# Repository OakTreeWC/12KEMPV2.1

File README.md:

# 12KEMP V2.1  (Complete)
12KEMP V2.1 is a 12 key 4 by 3 macropad, that features a Xiao SEEED Studio RP2040 with vial-qmk support, a clickable rotary encoder, a completely custom pcb with hot-swap support for 3/5-pin regular MX switches, as well as a complete case. All related files are in this repo, and you may create any form of case to mount the pcb onto, though it may take some time. Additionally, a bill of materials (BOM) is included. 

I made this project, 1. for school, and 2. for the [hackclub blueprint](https://blueprint.hackclub.com) event.

## Installing the Firmware
In order to install the firmware on the SEEED Studio RP2040 (RP2350 is not supported in QMK yet), hold the boot button on the microcontroller while plugging it into your computer. Once plugged in, a USB Mass Storage Device should appear. Download and move the .uf2 [firmware file](https://github.com/OakTreeWC/12KEMPV2.1/raw/refs/heads/main/Production/firmware.uf2) to the device. After the firmware has been put on the flash, the microcontroller should restart automatically. The firmware has now been installed.

## Usage
In order to use this project, one can either download Vial from [get.vial.today](https://get.vial.today), or use their [web interface](https://vial.rocks/). When plugged in, the device should show up on the top in a little dropdown. (Web users may have to manually select the device when setting up) If necessary, select the device from the dropdown. Now you can manually change what each key on the macropad does, simply by clicking the key you want to change and selecting what you want it to do from the bottom. You can change what keys on the other layers do as well, by just clicking the numbers right under the dropdown on the left.

## Bill of Materials
|Item                  |Description                                                                        |Qty.|Unit Price (USD)|Total Price  (USD)|URL                                                                                                                                                                                                                                                                                                                                                                                                                                                                                                         |Running Total (USD + Tax)|
|----------------------|-----------------------------------------------------------------------------------|----|----------------|------------------|------------------------------------------------------------------------------------------------------------------------------------------------------------------------------------------------------------------------------------------------------------------------------------------------------------------------------------------------------------------------------------------------------------------------------------------------------------------------------------------------------------|-------------------------|
|XIAO RP2040    |ARM® Cortex®-M0+ MCU 32-Bit Embedded Evaluation Board                              |1   |$4.68           |$4.68             |https://www.digikey.com/en/products/detail/seeed-technology-co-ltd/102010428/14672129                                                                                                                                                                                                                                                                                                                                                                                                                       |$5.16                    |
|Rotary Encoder        |Rotary Encoder Incremental 24 Quadrature (Incremental) Horizontal                  |1   |$1.72           |$1.72             |https://www.digikey.com/en/products/detail/bourns-inc/PEC12R-4020F-S0024/4699271                                                                                                                                                                                                                                                                                                                                                                                                                            |$7.06                    |
|Reverse Neopixels     |Addressable Lighting - 10 LED Discrete Red, Green, Blue (RGB)                      |2   |$2.95           |$5.90             |https://www.digikey.com/en/products/detail/adafruit-industries-llc/4960/14302512                                                                                                                                                                                                                                                                                                                                                                                                                            |$13.56                   |
|Akko Keyboard Switches|Akko V3 Creamy Yellow Pro Keyboard Switch, 5-Pin 50gf Linear Switches (45pcs)      |1   |$12.99          |$12.99            |https://www.amazon.com/Akko-Keyboard-Dustproof-Mechanical-Switches/dp/B0C3H8NVJV                                                                                                                                                                                                                                                                                                                                                                                                                            |$27.88                   |
|Schottky Diodes       |Diode 30 V 200mA Surface Mount 0603                                                |12  |$0.10           |$1.18             |https://www.digikey.com/en/products/detail/taiwan-semiconductor-corporation/TSS54U-RGG/7360711                                                                                                                                                                                                                                                                                                                                                                                                              |$29.18                   |
|Resistor              |For Neopixel Data Line. 379 Ohms ±0.1% 0.1W, 1/10W Chip Resistor 0603 (1608 Metric)|1   |$0.12           |$0.12             |https://www.digikey.com/en/products/detail/koa-speer-electronics-inc/RN73R1JTTD3790B25/10016392                                                                                                                                                                                                                                                                                                                                                                                                             |$29.31                   |
|PCB                   |PCB Manufactured by JLCPCB. White, 1.6mm, HASL w/ lead                             |5   |$1.32           |$6.60             |https://jlcpcb.com                                                                                                                                                                                                                                                                                                                                                                                                                                                                                          |$36.59                   |
|Lower Case            |Case Manufactured by JLC3DP. Black Resin                                           |1   |$12.47          |$12.47            |https://jlc3dp.com                                                                                                                                                                                                                                                                                                                                                                                                                                                                                          |$50.34                   |
|Upper Case            |Case Manufactured by JLCPCB. Grey Resin                                            |1   |$2.51           |$2.51             |https://jlc3dp.com                                                                                                                                                                                                                                                                                                                                                                                                                                                                                          |$53.11                   |
|Keycaps               |DSA Keycaps White 24pcs                                                            |1   |$8.99           |$8.99             |www.amazon.com/Mechkeeb-Profile-Switches-Keyboard-Replacement/dp/B0BWDTBF1L                                                                                                                                                                                                                                                                                                                                                                                                                                 |$63.02                   |
|Rotary Encoder Knob   |Aluminum Rotary Encoder Knob 2pcs                                                  |1   |$8.99           |$8.99             |www.amazon.com/Szliyands-Aluminum-Electronic-Potentiometer-Knob，Switch/dp/B099PX52LW                                                                                                                                                                                                                                                                                                                                                                                                                        |$72.93                   |
|Threaded Inserts      |M3 Threaded Inserts 152pcs                                                         |1   |$6.99           |$6.99             |https://www.amazon.com/Vibit-Threaded-Soldering-Printing-Components/dp/B0FWWW8VP1/ref=sr_1_3                                                                                                                                                                                                                                                                                                                                                                                                                |$80.64                   |
|Machine Screws        |M3 Screw Kit                                                                       |1   |$9.99           |$9.99             |https://www.amazon.com/Fgruh-750PCS-Assortment-Washers-Assorted/dp/B0FGV5FCBN/ref=sr_1_3?crid=2UNAGQJ7TRSPF&dib=eyJ2IjoiMSJ9.T3HWVrCMzkskj4FDtvfCYjAhiKf2eIXJNrTn39_bFjBR1J806O1NskeC_TrNL2d-0_rv4c3tJ2WiIqImzYRsNdlKskiq_KPhw2MnuLHrr7ROWvp0aYAezCjHHAfx-j9R1FgRYMZR6z3j6DWbe_FTcKSI5cNCdqJEDhLnH9UyM0u5ed6Of07kpRqKBp5WkTLn8qUsW4GWJz8Y-hXZX6mGeCbl1zGSf24ox8LtrZCSgZs.QTs0QwFb8cDs_wXvUWLPa0GUjuv97zXGykg1SJQzuNE&dib_tag=se&keywords=m3+screw+set&qid=1771132139&sprefix=m3+screw+set%2Caps%2C211&sr=8-3|$91.65                   |
|Digikey Shipping      |                                                                                   |1   |$4.99           |$4.99             |                                                                                                                                                                                                                                                                                                                                                                                                                                                                                                            |$97.15                  |
|JLC Shipping          |                                                                                   |1   |$10.73          |$10.73             |                                                                                                                                                                                                                                                                                                                                                                                                                                                                                                            |$108.98                  |

## Licensing

Copyright 2026 William C.

Licensed under the Apache License, Version 2.0 (the "License");
you may not use this file except in compliance with the License.
You may obtain a copy of the License at

http://www.apache.org/licenses/LICENSE-2.0

Unless required by applicable law or agreed to in writing, software
distributed under the License is distributed on an "AS IS" BASIS,
WITHOUT WARRANTIES OR CONDITIONS OF ANY KIND, either express or implied.
See the License for the specific language governing permissions and
limitations under the License.

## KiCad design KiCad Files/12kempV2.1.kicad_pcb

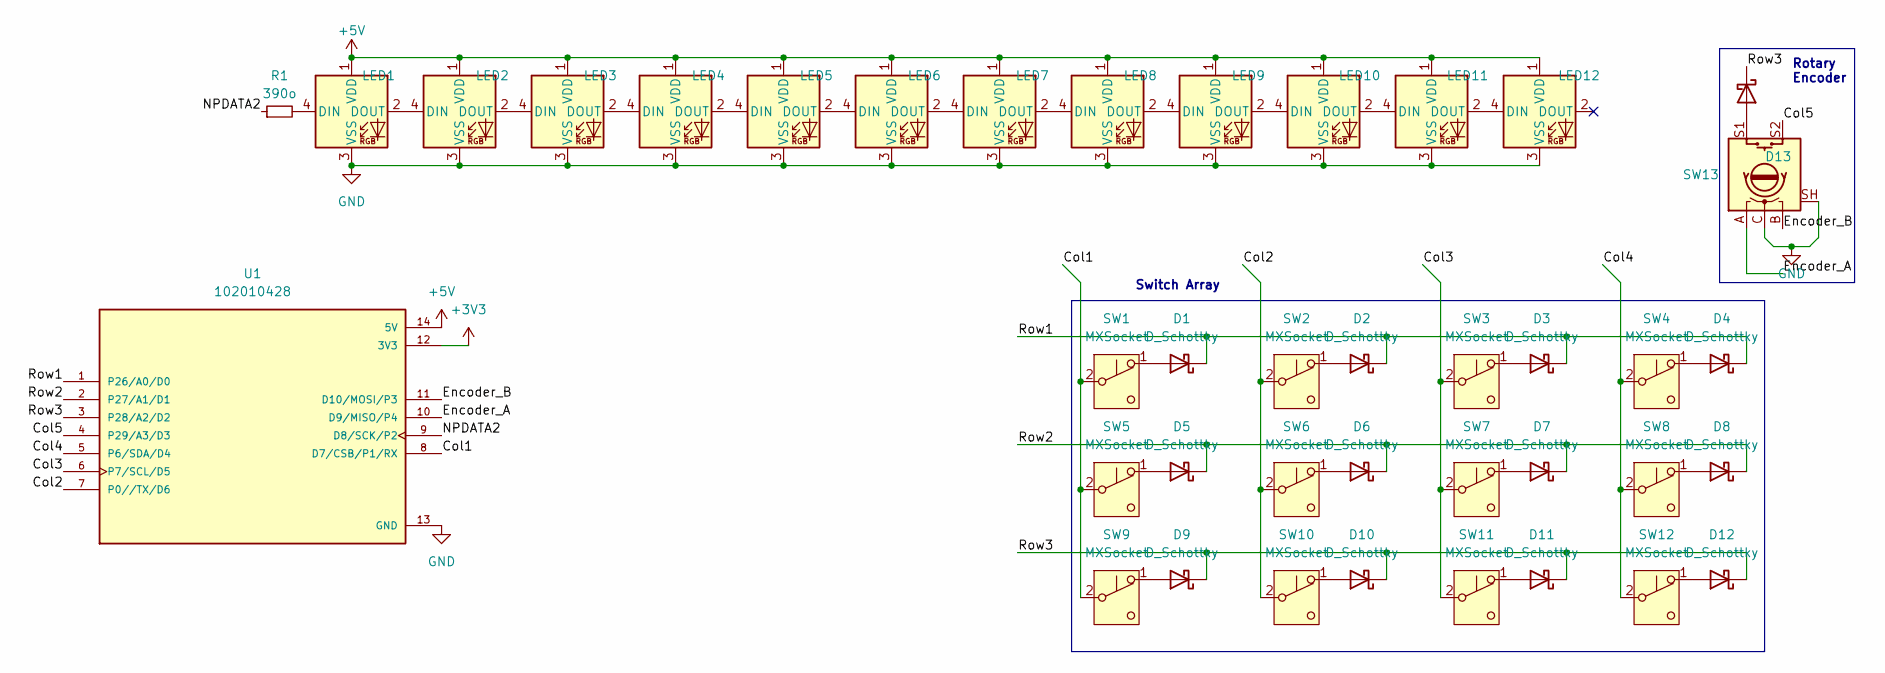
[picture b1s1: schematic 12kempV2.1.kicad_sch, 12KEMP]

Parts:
D1, D2, D3, D4, D5, D6, D7, D8, D9, D10, D11, D12, D13: D_Schottky; D_0603_1608Metric_Pad1.05x0.95mm_HandSolder
LED1, LED2, LED3, LED4, LED5, LED6, LED7, LED8, LED9, LED10, LED11, LED12: NeoPixel_THT; 4960_ADA
R1: 390o; R_0603_1608Metric_Pad0.98x0.95mm_HandSolder
SW1, SW2, SW3, SW4, SW5, SW6, SW7, SW8, SW9, SW10, SW11, SW12: MXSocket; Kailh_socket_MX
SW13: RotaryEncoder_Switch; RotaryEncoder_Bourns_Vertical_PEC12R-3x17F-Sxxxx
U1: 102010428; MODULE_102010428; PARTREV 1.3

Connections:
+3V3: U1.12 (3V3)
+5V: LED1.1 (VDD), LED2.1 (VDD), LED3.1 (VDD), LED4.1 (VDD), LED5.1 (VDD), LED6.1 (VDD), LED7.1 (VDD), LED8.1 (VDD), LED9.1 (VDD), LED10.1 (VDD), LED11.1 (VDD), LED12.1 (VDD), U1.14 (5V)
/Col1: SW1.2 (B), SW5.2 (B), SW9.2 (B), U1.8 (D7/CSB/P1/RX)
/Col2: SW2.2 (B), SW6.2 (B), SW10.2 (B), U1.7 (P0//TX/D6)
/Col3: SW3.2 (B), SW7.2 (B), SW11.2 (B), U1.6 (P7/SCL/D5)
/Col4: SW4.2 (B), SW8.2 (B), SW12.2 (B), U1.5 (P6/SDA/D4)
/Col5: SW13.S2, U1.4 (P29/A3/D3)
/Encoder_A: SW13.A, U1.10 (D9/MISO/P4)
/Encoder_B: SW13.B, U1.11 (D10/MOSI/P3)
/NPDATA2: R1.1, U1.9 (D8/SCK/P2)
/Row1: D1.1 (K), D2.1 (K), D3.1 (K), D4.1 (K), U1.1 (P26/A0/D0)
/Row2: D5.1 (K), D6.1 (K), D7.1 (K), D8.1 (K), U1.2 (P27/A1/D1)
/Row3: D9.1 (K), D10.1 (K), D11.1 (K), D12.1 (K), D13.1 (K), U1.3 (P28/A2/D2)
GND: LED1.3 (VSS), LED2.3 (VSS), LED3.3 (VSS), LED4.3 (VSS), LED5.3 (VSS), LED6.3 (VSS), LED7.3 (VSS), LED8.3 (VSS), LED9.3 (VSS), LED10.3 (VSS), LED11.3 (VSS), LED12.3 (VSS), SW13.C, SW13.SH (SHIELD), U1.13 (GND)
unnamed: D1.2 (A), SW1.1 (A)
unnamed: D2.2 (A), SW2.1 (A)
unnamed: D3.2 (A), SW3.1 (A)
unnamed: D4.2 (A), SW4.1 (A)
unnamed: D5.2 (A), SW5.1 (A)
unnamed: D6.2 (A), SW6.1 (A)
unnamed: D7.2 (A), SW7.1 (A)
unnamed: D8.2 (A), SW8.1 (A)
unnamed: D9.2 (A), SW9.1 (A)
unnamed: D10.2 (A), SW10.1 (A)
unnamed: D11.2 (A), SW11.1 (A)
unnamed: D12.2 (A), SW12.1 (A)
unnamed: D13.2 (A), SW13.S1
unnamed: LED1.4 (DIN), R1.2
unnamed: LED1.2 (DOUT), LED2.4 (DIN)
unnamed: LED2.2 (DOUT), LED3.4 (DIN)
unnamed: LED3.2 (DOUT), LED4.4 (DIN)
unnamed: LED4.2 (DOUT), LED5.4 (DIN)
unnamed: LED5.2 (DOUT), LED6.4 (DIN)
unnamed: LED6.2 (DOUT), LED7.4 (DIN)
unnamed: LED7.2 (DOUT), LED8.4 (DIN)
unnamed: LED8.2 (DOUT), LED9.4 (DIN)
unnamed: LED9.2 (DOUT), LED10.4 (DIN)
unnamed: LED10.2 (DOUT), LED11.4 (DIN)
unnamed: LED11.2 (DOUT), LED12.4 (DIN)

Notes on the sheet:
Rotary Encoder
Switch Array

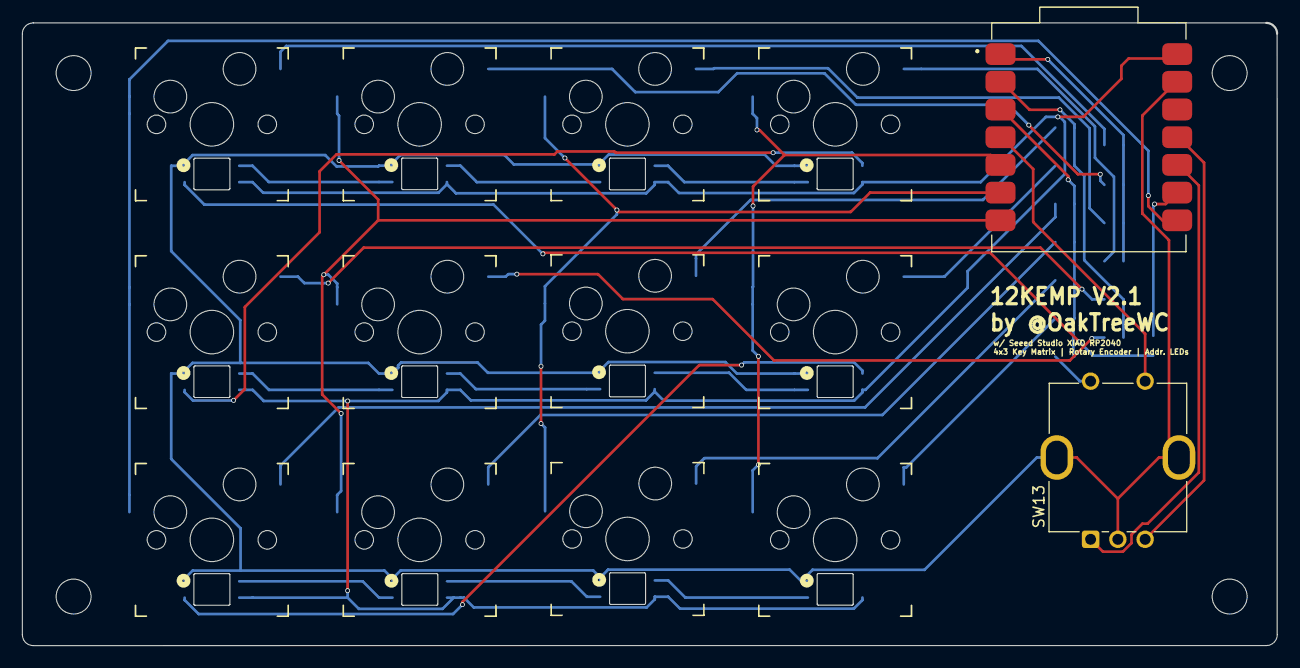
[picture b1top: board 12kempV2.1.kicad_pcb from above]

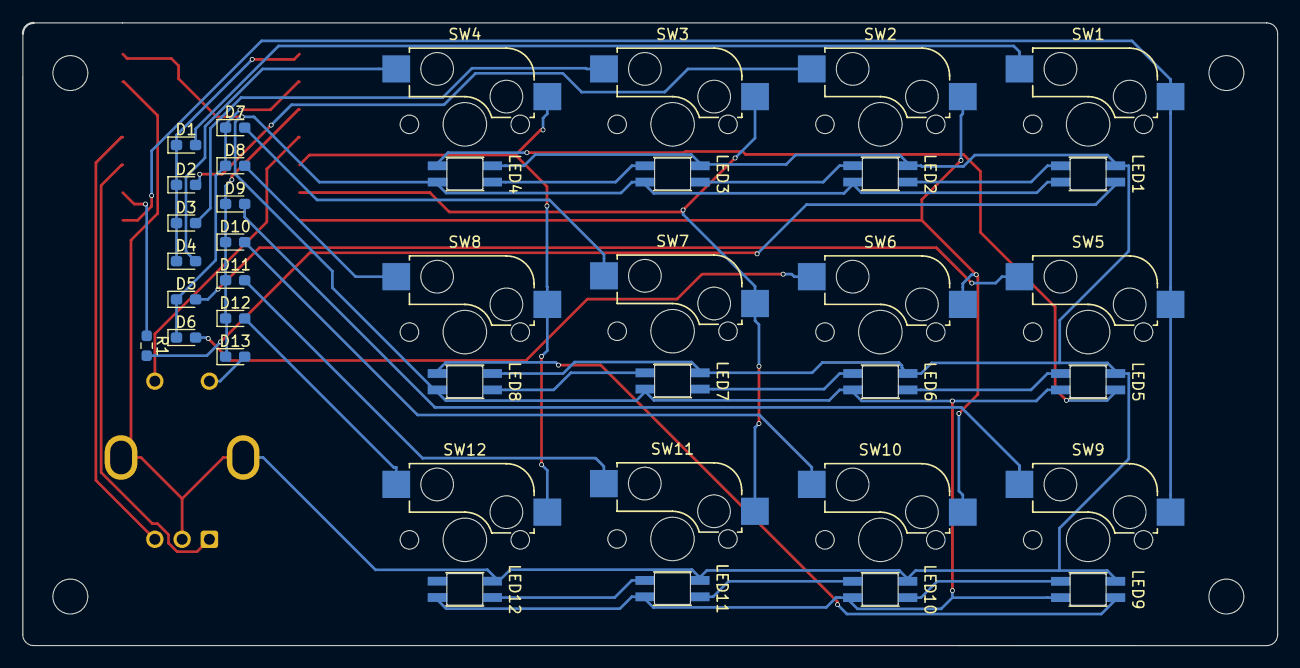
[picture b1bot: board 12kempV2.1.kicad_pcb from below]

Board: 2 copper layers, 115.0 x 57.1 mm, 40 parts (26 on the bottom side), 38 nets.

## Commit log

2026-02-10 Update README with new hardware details
    Updated project description to reflect changes in hardware.
2026-02-10 Fix typo in README for RP2040 LCD model
2026-02-15 Init Commit
2026-02-15 Added BOM
2026-02-15 Revise README with new hardware details and BOM
    Updated project description and added Bill of Materials.
2026-02-15 Fix shipping cost entries in BOM
    Updated shipping costs for Digikey and JLC.
2026-02-15 Update README with usage instructions for Vial
    Added instructions for using the project with Vial.
2026-02-15 Fix markdown link syntax in README.md
2026-02-15 Fixed a typo in the BOM
2026-02-15 Modified the gitignore
2026-02-20 Organized the kicad files and fixed an error in the PCB
2026-02-20 Added another folder to the commit
2026-02-20 Edited the .gitignore
2026-02-22 Added complete step file
2026-02-23 Added schematic pic
2026-02-24 move
2026-02-24 firmware lwk in the wrong folder
2026-02-24 Add new image to README
    Added an additional image to the README.
2026-03-09 Update project status to 'Complete' in README
2026-03-24 Update README with firmware installation and usage
    Added sections for installing firmware and usage instructions.
2026-04-02 Update copyright year and owner in LICENSE file
2026-04-03 photos
2026-05-04 fixed white balance of photo
